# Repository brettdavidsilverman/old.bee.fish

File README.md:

# bee.fish
Files to create bee.fish website

This contains all the files used to research and design https://bee.fish

The files under /server are used to create an actual https server.

Install these tools and libraries</br>
   sudo apt install build-essential</br>
   sudo apt install libssl-dev</br>
   sudo apt install libboost-all-dev</br>
   sudo apt install libcrypto++-dev</br>

Copy bee.fish/dev.config.h to the parent directory and
rename it as config.h . Customise this file.

Use the <b>make</b> command to build the C++ programs.

Then <b>make install</b>

The rest of the files are html or js and provide examples of what I've been researching.
The /client directory has the layers needed to create the /client/draw app (work in progress).

The /server/database directory has files needed to create a bit hierarchical database.
Currently the https://bee.fish/client/storage program uses it as key/value pair database.

The https://bee.fish/Arduino directories contain ESP32 files for the https://bee.fish/beehive/ camera (work in progress)

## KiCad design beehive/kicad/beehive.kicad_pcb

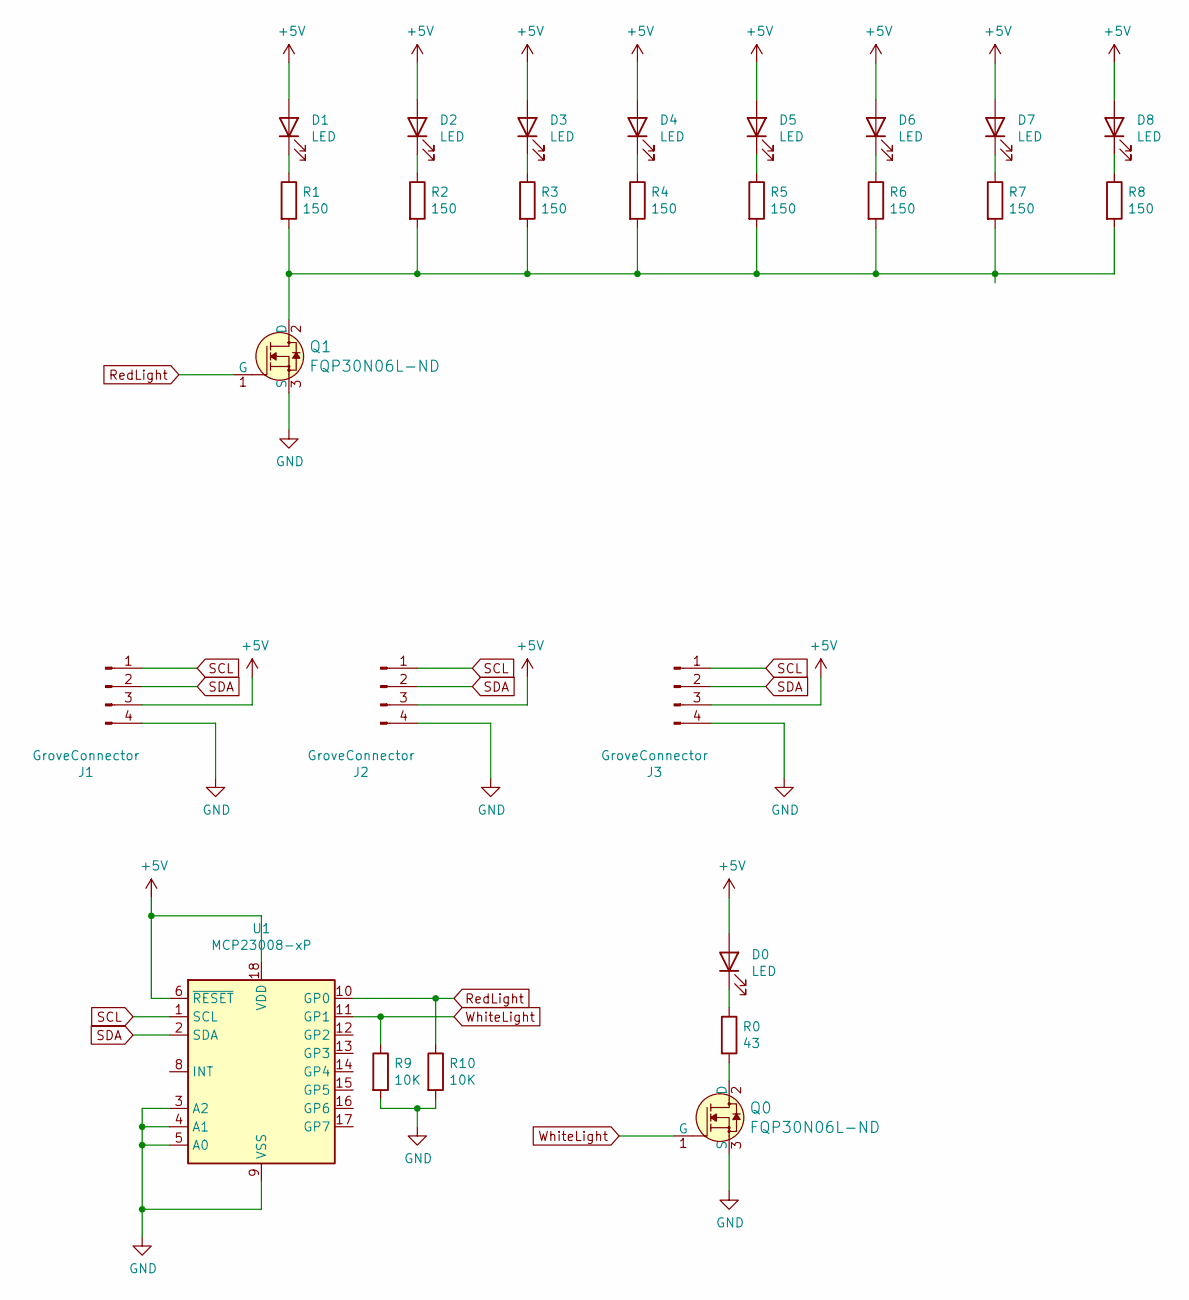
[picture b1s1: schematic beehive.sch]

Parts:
D0: LED; LED_Rectangular_W7.62mm_H4.55mm_P5.08mm_R3
D1, D2, D3, D4, D5, D6, D7, D8: LED; LED_D10.0mm
J1, J2, J3: GroveConnector; SEEED_110990030; PARTREV A
Q0, Q1: FQP30N06L-ND; TO-220-3_Horizontal_TabDown
R0: 43; R_Axial_DIN0207_L6.3mm_D2.5mm_P10.16mm_Horizontal
R1, R2, R3, R4, R5, R6, R7, R8: 150; R_Axial_DIN0207_L6.3mm_D2.5mm_P10.16mm_Horizontal
R9, R10: 10K; R_Axial_DIN0207_L6.3mm_D2.5mm_P10.16mm_Horizontal
U1: MCP23008-xP; DIP-18_W7.62mm

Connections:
+5V: D0.2 (A), D1.2 (A), D2.2 (A), D3.2 (A), D4.2 (A), D5.2 (A), D6.2 (A), D7.2 (A), D8.2 (A), J1.3, J2.3, J3.3, U1.6 (~RESET), U1.18 (VDD)
GND: J1.4, J2.4, J3.4, Q0.3 (S), Q1.3 (S), R9.2, R10.2, U1.3 (A2), U1.4 (A1), U1.5 (A0), U1.9 (VSS)
unnamed: D0.1 (K), R0.1
unnamed: D1.1 (K), R1.1
unnamed: D2.1 (K), R2.1
unnamed: D3.1 (K), R3.1
unnamed: D4.1 (K), R4.1
unnamed: D5.1 (K), R5.1
unnamed: D6.1 (K), R6.1
unnamed: D7.1 (K), R7.1
unnamed: D8.1 (K), R8.1
unnamed: Q0.2 (D), R0.2
unnamed: Q1.2 (D), R1.2, R2.2, R3.2, R4.2, R5.2, R6.2, R7.2, R8.2
RedLight: Q1.1 (G), R10.1, U1.10 (GP0)
SCL: J1.1, J2.1, J3.1, U1.1 (SCL)
SDA: J1.2, J2.2, J3.2, U1.2 (SDA)
WhiteLight: Q0.1 (G), R9.1, U1.11 (GP1)

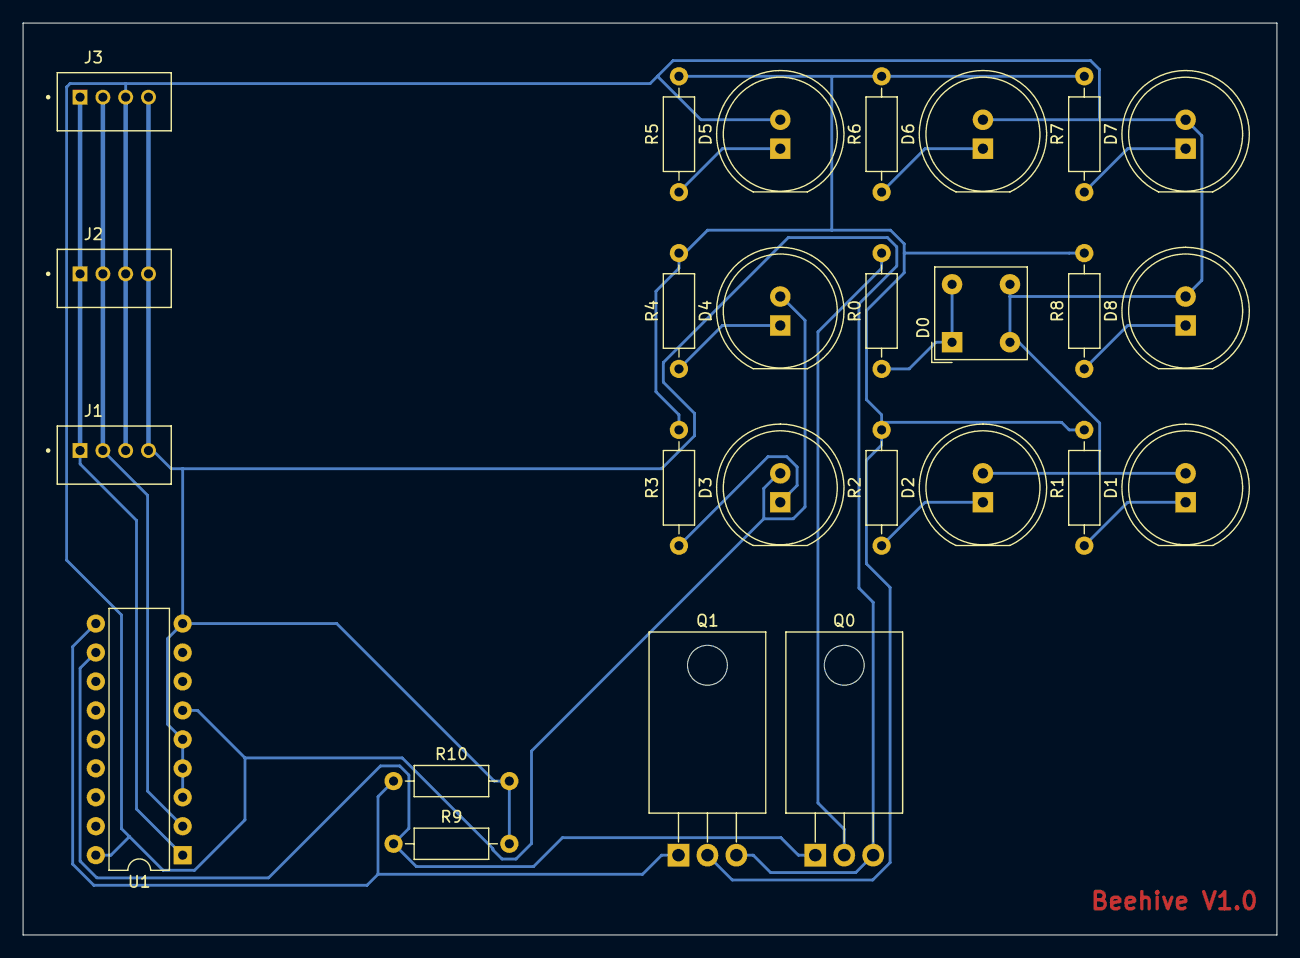
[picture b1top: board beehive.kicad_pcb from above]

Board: 2 copper layers, 110.0 x 80.0 mm, 26 parts (0 on the bottom side), 17 nets.

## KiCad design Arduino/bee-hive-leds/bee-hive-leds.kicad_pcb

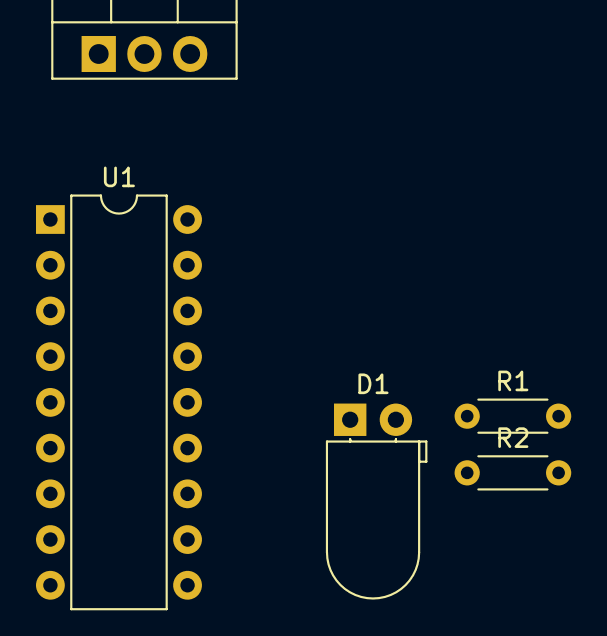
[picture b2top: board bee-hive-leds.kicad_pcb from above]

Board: 2 copper layers, 5 parts (0 on the bottom side), 5 nets, no tracks yet.

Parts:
D1: LED; LED_D5.0mm_Horizontal_O1.27mm_Z3.0mm_Clear
Q1: IRF1405N; TO-220-3_Vertical
R1: 10K; R_Axial_DIN0204_L3.6mm_D1.6mm_P5.08mm_Horizontal
R2: 33; R_Axial_DIN0204_L3.6mm_D1.6mm_P5.08mm_Horizontal
U1: MCP23008-xP; DIP-18_W7.62mm

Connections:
+5V: U1.6, U1.18
GND: Q1.3, R1.2, U1.3, U1.4, U1.5, U1.9
unnamed: D1.1, Q1.2
unnamed: D1.2, R2.2
unnamed: Q1.1, R1.1, U1.10

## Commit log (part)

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2022-07-10 Making beehive index impervious
2022-07-11 Added light web server to toggle light.
2022-07-11 Added label option to serial command line
2022-07-11 Fixed wifi to allow re-connect
2022-07-11 Fixed resetConnection
2022-07-11 camera reset
2022-07-11 Set upload weather timer to 5 minutes
2022-07-12 Fixed bug with file size in file system
2022-07-12 Added flag to prevent up and down connections simultaneously
2022-07-12 Working on reloading camera
2022-07-12 Config.h errors
2022-07-12 Added setInterval to set camera img src
2022-07-12 Added complete check for camera img reload
2022-07-12 Removed timer reload
2022-07-12 Cleaning up camera url page
2022-07-12 Trialing beehive index
2022-07-13 Finetuning beehive index
2022-07-15 Full Stack including upload and get weather
2022-07-15 Added lock guard to send/receive on sslconnection and web server
2022-07-16 Working
2022-07-17 Added READ_WEATHER, removed wifiserver library. Uses default one
2022-07-17 Removed lock guard. Simplified wifi
2022-07-17 Simplified _connection and removed command loop
2022-07-18 Fixed random data bug
2022-07-21 Full stqack. Bit buggy but restarts
2022-07-22 Added buffering from chunked to send
2022-07-22 Reorganized internet and internet web server
2022-07-22 DEBUG to laptop works well
2022-07-22 Added crypto sample page
2022-07-22 Added server encryption shell
2022-07-24 Changed FRAME_BUFFER_COUNT to 4. Getting goog rate
2022-07-28 Switched to bee.fish non debug mode
2022-07-28 Added origin to beehive/test.html fetch
2022-07-31 Simplified id
2022-07-31 Set quality to 5 for capture and getimage
2022-07-31 Merged cookie back to master
2022-08-05 Framework for updating flash from cloud
2022-08-06 Migrated to bee.fish
2022-08-06 Merging to v1.0
2022-08-07 Time added. Id now has seconds and milliseconds seperate
2022-08-08 Added RTC example and fix rtc libraries
2022-08-09 About to fix archiving of web parts
2022-08-09 Removed adc-channel.h and it still works
2022-08-09 Removed adc-chcannel.h
2022-08-09 Moved web-client2.h to web-client.h
2022-08-09 Moved web-server-base2.h to web-server-base.h
2022-08-11 orked on own WiFiManager. RTC and battery work. Still buggy
2022-08-11 RTC OK. Own WiFiManager still bit buggy
2022-08-14 Merging with master
2022-08-14 Compiled for bee.fish
2022-08-19 Added test case for json in streamer
2022-08-20 moving json streams to b-script
2022-08-20 Pagesize and errant test case.
2022-08-20 Fixed missing SERVER
2022-08-20 Added working rtc wakeup project
2022-08-23 Everything working but POST image
2022-08-23 Getting framerates of 25.0
2022-08-23 Got bee.fish.local to work
2022-08-25 Storage now has content-type and allows for post to id in query
2022-08-25 POST to id with contenttype storage works
2022-08-26 Most works except rtc buggy and upload image not tested
2022-08-27 All testts passed with character-bits
2022-08-27 Tests pass in arduino
2022-08-27 Storage/Data buggy, but web server works
2022-08-28 Power encoding works
2022-08-28 Added != support for BStrings
2022-08-29 b-string bug fixes
2022-09-01 Need to fix stack back up. Work In Prograess
2022-09-03 Removing bit-char
2022-09-03 Camera working again
2022-09-04 RTC Working ok
2022-09-04 Upload/download of image ok
2022-09-04 Migrating to live
2022-09-04 Added explicit TwoWire for multiplexer, and weather
2022-09-05 c code for rtc. Works nicely
2022-09-05 Full stack, but memory issues
2022-09-07 Pushed directories up a dir
2022-09-07 Added conditionals to database files
2022-09-08 fixed segmentation fault bug. Added reconnect func to wifi
2022-09-08 Upgraded Arduino
2022-09-09 Added time zone to feebee-cam setup
2022-09-09 Added parts.csv (someone deleted original)
2022-09-10 Modified log. Added key support for get requests in storage app
2022-09-13 New restful storage works
2022-09-13 Compile for live
2022-09-14 Fixed download file bug. Added label to timezones
2022-09-15 Increased default settings to 15 min for check
2022-09-15 modified: beehive/index.html
2022-09-15 Added formatJSON
2022-09-15 Formatted beehive index page
2022-09-15 Trying to fix pesky degrees bug
2022-09-15 Migrating back to dev
2022-09-15 Added label to url object in weather
2022-09-15 Modified authentication-app.h
2022-09-17 Moved feebee-cam.ino to /home/bee/bee.fish/feebee-cam
2022-09-18 Added count down to beehive console
2022-09-19 Simplified count down. Simplified weather, and added extended parameter
2022-09-21 Added battery to default weather. Added authenticate.js. Moved beehive/logon to beehive/logon.bak
2022-09-21 Moved authenticate to authentication.js. Added authenticate to beehive. Modified getCountDown to function after getSettings.
2022-09-21 Added degree symbol to weather temperature unit. Still bugs on web page
2022-09-21 Modified exception handler for logon index.html
2022-09-21 Logon reloads if no redirect specified
2022-09-22 Moving to live
2022-09-22 Reworked string library. Fixed degrees. Fixed missing byte in images
2022-09-26 Added wakeupTime instead of checkEvery.
2022-09-26 Added more time-zones.json
2022-09-27 Removed precision from json write out
2022-09-27 Moved escaped degree to actual degree symbol in weather
2022-09-27 Now uploades weather/image on every internet connection
2022-10-01 Added extended to weather upload and to formatJSON.js
2022-10-02 Added extended to formatJSON. Fixed extraneous comma in undefined object parameters. Reverted BStream to override ostream
2022-10-02 Made setup lastError top and bold
2022-10-02 Moved next wake up time to top of index.html
2022-10-02 Added space to last line of beehive console index.html
2022-10-04 Added google console link to main index.html
2022-10-04 Added restart message to complete firmware upgrade
2022-10-08 Branching to b-string changes
2022-10-08 Removed content-type check from storage-app in https
2022-10-08 Create new task on each web client request.
2022-10-08 Removed authentication from camera default page
2022-10-08 Debugging
2022-10-08 Updating
2022-10-08 Removed authentication from beehive.html
2022-10-10 Checking out v1.2
2022-10-11 Revert "wip"
    This reverts commit 6de0c8a6bbdced87ed0b61e4bb6577cd145c675a.
2022-10-16 Revokinbg partitions.csv
2022-10-16 modified partions.csv but still no joy
2022-10-17 Updated b-script/object.h
2022-10-19 Revoked b-string, working well
2022-10-19 web-response, web-request ok
2022-10-19 Added b-string/stream.h
2022-10-19 Added b-string/base64.h
2022-10-19 Added data.h
2022-10-21 Isolated bug to b-string.h. Fixed compiler warnings with ostream& and object&
2022-10-21 Added decodeURI to b-string
2022-10-22 Removed most static. Still buggy with _utf8 character in b-string
2022-10-22 All works, but string class not thread safe
2022-10-22 b-string minus utf8 member variable. Works well.
2022-10-24 Copied b-string to master
2022-10-24 Tested compile. Fixe a few issues with webserver
2022-10-29 Removed loop upload. Cleaned debug messages. Added (untested) time. Light returne to normal.
2022-10-30 Removed branches
2022-10-30 Added more debug msgs to no id and no key in storage-app
2022-10-31 Added extra error checks for web-client write. Moved web-server camera to core -1.
2022-10-31 Fixed extended-weather bug. Modified WebRequest URl Query to parse key value pairs
2022-11-01 Migrated settings/setup to status/setup. Decoupled commands. Removed redundant individual functions inplace of commands
2022-11-01 Restart works smoothly and redirects from setup page
2022-11-01 working on just resetting camera settings, not wifi settings
2022-11-01 Reset works on camera page.
2022-11-01 Removed 'live' weather and image updates to make it more robust.
2022-11-03 Going to live
2022-11-04 Seperated upload functionality. Working
2022-11-04 Adding extra weather sensor
2022-11-05 Error loading beehive page
2022-11-05 Added typed variables to web-client create task. Set stack size to 4000 from 5000. Works nicely
2022-11-05 Migrating to bee.fish
2022-11-06 Sensor add/remove works ok. Changed multiplexer to mainBoardTwoWire. Moved camera flushFrameBuffer to setup.applyToCamera
2022-11-07 Added robustness to beehive/index.html saveStatus
2022-11-07 Fixed file truncation by reinstating flush to web-request
2022-11-07 Added caching back on
2022-11-07 Readded keep-alive
2022-11-08 Reset and posting to live
2022-11-16 UNTESTED
2022-11-16 Still buggy on camera pruning Untested but going live just to have something to do.
2022-11-22 migrating to two.bee.fish
2022-11-22 Added detailed messages to httos/server.ht startup
2022-11-24 Moved initializeLogs in server to laster on. Increased frame rate by changing priority of task.
2022-11-24 Formatted IP Address. Added download status to serial
2022-11-24 Moved all loops to core 0. Camera kept at core 1
2022-12-14 Reconciling weather in beehive-index.html
2022-12-14 Put weather back.
2022-12-19 Added connecttest.txt
2022-12-24 Remove rtc. Added restart of web-server. Removed initialize from light and weather, now in constructor.
2022-12-26 Fixed up some log formatting. Switched off internet after error. Updated putToSleep to handle internet errors.
2022-12-26 Cant use insecure in secure host
2022-12-29 Added targe for b-script in https/Makefile
2022-12-29 Removed uploads when running camera
2023-01-02 Added sample dev.config.h to bee.fish
2023-01-02 Added assignmemt operator and cast operator to path. Added test cases for string and int.
2023-01-03 Moved https sudo from make install to make
2023-01-03 Changed file and database to use BString
2023-01-04 Added parent field to database branch
2023-01-05 storage-app clears data on delete Removed unused variables from path
2023-01-05 Added inage nav buttons to beehive index
2023-01-08 Runs at 25-30fps. Replaced delay with taskYIELD Switched off upload whilst camera running
2023-01-09 Tightened up web server to connections of 1 Added socketLock to upload vs web-server Status now gets its label from _setup Restart after error now puts to sleep for 10 seconds (defined in config.h) W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
2023-01-09 Added wait for connection function to wifi. Used generically Replaced socket lock mutex with boolean. Works really well
2023-01-13 Weather and video work well. Added host and feebeecan ssids and passwords to setup and serial
2023-01-14 Tuning beehive index startup
2023-01-14 Pause camera on weather. Works well
2023-01-14 Modified start camera loop in beehive index
2023-01-14 Removed stop then start from beehive index.
2023-01-18 Merging Timer-CAM and web-cam to replace feebee-cam. Great frame rate and stable http
2023-01-27 Upgrading web-server to use esp32 libraries
2023-01-27 Moved time-zones to own file. Added workaround for parsing to allow this large file to work. Not ideal
2023-01-27 Moved TimerCam library to sketch folder. Setup now works with change of password. Removed wait from ssid.
2023-01-27 Reinstated command:loop and task. Removed comments from web-storage
2023-01-29 Mess
2023-01-30 Merging from socket to inbuilt httpd. Commands done.
2023-02-03 Added red page
2023-02-04 Moving feebee-cam.ino to live
2023-02-06 Various. Migratinng to live
2023-02-08 Download binary image from setup works WiFi reconnects after disconnect
2023-02-08 Moved from debug to live
2023-02-11 Various bug fixes
2023-02-19 Set status.url correctly.
2023-02-19 Restarts after error when saving status
2023-02-21 File system download file now returns false if file download fails
2023-02-21 Fixed bug with conversion from formatJSON to formatWeather
2023-02-21 Updated manifest.json version
2023-02-21 Moved initializeMemory back to the top of feebee-cam.ino
2023-02-21 RESTART_AFTER_ERROR to web request on send err
2023-03-13 Fixed bug with storage id in client/storage. Time always initializes regardless. Removed extraneous comments from commmand
2023-03-13 Added connecttest.txt to beehive.
2023-03-13 Modified contents of connecttest.txt
2023-03-15 Moved camera stream to ...:81
2023-03-20 Serial command line defaults to "help" if nothing selected.
2023-03-26 Modified debug output of locac-time
2023-03-26 Testing file setup
2023-03-26 added reason to RESTART_AFTER_ERROR
2023-04-10 Compute engine
